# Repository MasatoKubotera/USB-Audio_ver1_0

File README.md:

<html lang="en">
  <head>
    <meta charset="uft-8">
    <meta name="author" content="Masato Kubotera">
  </head>
  <body>
    <h1>USB-Audio Ver. 1.0</h1>
    <h2>About USB-Audio</h2>
    <p>
      USB-Audio is the USB device for audio input/output via a USB interface.
      <br><br>
      <h3>About Ver. 1.0</h3>
      Ver 1.0 has one port for speaker output and two condenser microphones. Since it does not have a speaker, it must be connected via a 2-pin XH connector if necessary. <br>
      The device is used by connecting it to a PC with a USB Mini-B cable.<br>
      The outputs have 0 dB attenuation and the inputs have 3.5 -dB attenuation.
      Each input and output has an "MFB LP filter".
      <br><br>
      <!--
      -->
      <table>
        <tr>
          <td>
            <a href="image/brd_top.png">
              <div align="center">
                
              </div>
            </a>
          </td>
          <td>
            <div align="center">
              
            </div>
          </td>
        </tr>
        <tr>
          <td>
            <div align="center">
              PCB preview image
            </div>
          </td>
          <td>
            <div align="center">
              After component mounting
            </div>
          </td>    
        </tr>
      </table>
    </p>
    <h2>Repository Contents</h2>
    <p>
    <dl>
      <dt>\image</dt>
      <dd>PCB preview images and capture of design screen</dd>
      <dt>\libraries</dt>
      <dd>Libraries used in Autodesk Eagle design</dd>
      <dt>Schematic.pdf</dt>
      <dd>Circuit diagram of this product</dd>
      <dt>BOM.txt</dt>
      <dd>Parts lists output from design data</dd>
      <dt>.brd</dt>
      <dd>Board wiring design file by Autodesk Eagle</dd>
      <dt>.sch</dt>
      <dd>Schematic design file by Autodesk Eagle</dd>
      <dt>Gerber_data.zip</dt>
      <dd>Zip folder of Gerber format files for PCB manufacturing requests.</dd>
      <dt>LICENSE</dt>
      <dd>This is a license to use this product. Please confirm before use.</dd>
      <dt>.gitignore</dt>
      <dd>File to exclude cache files from management.</dd>
    </dl>
    </p>
    <h2>Documentation</h2>
      <p>
        <h3>BOM</h3>
          <table>
            <thead>
              <tr>
                <th> Eagle Design Parts # </th>
                <th> Q'ty </th>
                <th> Mfr. Product # </th>
                <th> Supplier </th>
                <th> Description </th>
              </tr>
            </thead>
              <tr>
                <td>C1, C2, C3, C4, C7, C8, C9, C25</td>
                <td>8</td>
                <td>GRM188R71E105KA12</td>
                <td><a href="https://akizukidenshi.com/catalog/g/gP-14526/">Akizuki</a></td>
                <td>Multilayer Ceramic Capacitors SMD/SMT 1uF 25V 10% 0603</td>
              </tr>
              <tr>
                <td>C10, C13, C15, C16, C21, C22</td>
                <td>6</td>
                <td>UMW1V100MDD</td>
                <td><a href="https://akizukidenshi.com/catalog/g/gP-08377/">Akizuki</a></td>
                <td>Aluminum Electrolytic Capacitors - Radial Leaded 35volts 10uF 85c 5x5 2LS</td>
              </tr>
              <tr>
                <td>C11, C19, C20</td>
                <td>3</td>
                <td>GCD188R71H182KA01J</td>
                <td><a href="https://www.mouser.jp/ProductDetail/81-GCD188R71H182KA1J">Mouser</a></td>
                <td>Multilayer Ceramic Capacitors SMD/SMT 1800pF 50V 10% 0603</td>
              </tr>
              <tr>
                <td>C12, C17, C18</td>
                <td>3</td>
                <td>GRM1882C1H331JA01</td>
                <td><a href="https://akizukidenshi.com/catalog/g/gP-09254/">Akizuki</a></td>
                <td>Multilayer Ceramic Capacitors SMD/SMT 330pF 50V 5% 0603</td>
              </tr>
              <tr>
                <td>C14, C23</td>
                <td>2</td>
                <td>GRM188R6YA106MA73</td>
                <td><a href="https://akizukidenshi.com/catalog/g/gP-13161/">Akizuki</a></td>
                <td>Multilayer Ceramic Capacitors SMD/SMT 10uF 35V 20% 0603</td>
              </tr>
              <tr>
                <td>C24</td>
                <td>1</td>
                <td>GCM188L81H104K57</td>
                <td><a href="https://akizukidenshi.com/catalog/g/gP-16143/">Akizuki</a></td>
                <td>Multilayer Ceramic Capacitors SMD/SMT 0.1uF 50V 10% 0603</td>
              </tr>
              <tr>
                <td>C5, C6</td>
                <td>2</td>
                <td>C1608C0G1H220J080AA</td>
                <td><a href="https://www.mouser.jp/ProductDetail/810-C1608C0G1H220J">Mouser</a></td>
                <td>Multilayer Ceramic Capacitors SMD/SMT 22pF 50V 5% 0603</td>
              </tr>
              <tr>
                <td>CH1</td>
                <td>1</td>
                <td>S2B-XH-A(LF)(SN)</td>
                <td><a href="https://akizukidenshi.com/catalog/g/gC-12262/">Akizuki</a></td>
                <td>Connector Header Through Hole, Side entry 2 position 2.5mm</td>
              </tr>
              <tr>
                <td>CR1</td>
                <td>1</td>
                <td>FA-238V 12.0000MB-K3</td>
                <td><a href="https://akizukidenshi.com/catalog/g/gP-05225/">Akizuki</a></td>
                <td>Crystals 12.0000MHz 50ppm 10pF -40C +85C</td>
              </tr>
              <tr>
                <td>D1, D2</td>
                <td>2</td>
                <td>CG0603MLC-05E</td>
                <td><a href="https://www.mouser.jp/ProductDetail/652-CG0603MLC-05E">Mouser</a></td>
                <td>ESD Protectors 5V 0603</td>
              </tr>
              <tr>
                <td>D3</td>
                <td>1</td>
                <td>RB520SM-30T2R</td>
                <td><a href="https://www.mouser.jp/ProductDetail/755-RB520SM-30T2R">Mouser</a></td>
                <td>Schottky Diodes & Rectifiers Diode Schottky 30V 0.2A</td>
              </tr>
              <tr>
                <td>F1</td>
                <td>1</td>
                <td>MF-MSMF050-2</td>
                <td><a href="https://www.mouser.jp/ProductDetail/652-MF-MSMF050-2">Mouser</a></td>
                <td>PTC Resettable Fuses 15V .5A-HD 100A MAX</td>
              </tr>
              <tr>
                <td>FL1</td>
                <td>1</td>
                <td>BLM18SD220SN1D</td>
                <td><a href="https://www.mouser.jp/ProductDetail/81-BLM18SD220SN1D">Mouser</a></td>
                <td>Ferrite Beads 22 OHM 0603</td>
              </tr>
              <tr>
                <td>IC1</td>
                <td>1</td>
                <td>PCM2904DB</td>
                <td><a href="https://www.mouser.jp/ProductDetail/595-PCM2904DB">Mouser</a></td>
                <td>Interface - CODECs Ster Codec with USB Ifc Sngl-end I/O</td>
              </tr>
              <tr>
                <td>IC2, IC3</td>
                <td>2</td>
                <td>OPA2353UA</td>
                <td><a href="https://www.mouser.jp/ProductDetail/595-OPA2353UA">Mouser</a></td>
                <td>High Speed Operational Amplifiers Hi-Spd Single-Sply Rail-to-Rail</td>
              </tr>
              <tr>
                <td>IC4</td>
                <td>1</td>
                <td>REG103GA-AG4</td>
                <td><a href="https://www.mouser.jp/ProductDetail/595-REG103GA-AG4">Mouser</a></td>
                <td>LDO Voltage Regulators DMOS 500mA LDO Reg</td>
              </tr>
              <tr>
                <td>LED1, LED2</td>
                <td>2</td>
                <td>150060VS86000</td>
                <td><a href="https://www.mouser.jp/ProductDetail/710-150060VS86000">Mouser</a></td>
                <td>Standard LEDs - SMD Green 2V 20mA 573nm 0603</td>
              </tr>
              <tr>
                <td>MIC1, MIC2</td>
                <td>2</td>
                <td>C9767BB422LFP</td>
                <td><a href="https://akizukidenshi.com/catalog/g/gP-01810/">Akizuki</a></td>
                <td>2-wire Electret Condenser Microphone</td>
              </tr>
              <tr>
                <td>R1, R20</td>
                <td>2</td>
                <td>RC0603FR-101KL</td>
                <td><a href="https://www.mouser.jp/ProductDetail/603-RC0603FR-101KL">Mouser</a></td>
                <td>Thick Film Resistors - SMD 1 kOhms 100-200mW 1% 0603</td>
              </tr>
              <tr>
                <td>R11, R12, R13</td>
                <td>3</td>
                <td>RC0603FR-10100RL</td>
                <td><a href="https://www.mouser.jp/ProductDetail/603-RC0603FR-10100RL">Mouser</a></td>
                <td>Thick Film Resistors - SMD 100 Ohms 100-200mW 1% 0603</td>
              </tr>
              <tr>
                <td>R18, R19</td>
                <td>2</td>
                <td>RC0603FR-1018KL</td>
                <td><a href="https://www.mouser.jp/ProductDetail/603-RC0603FR-1018KL">Mouser</a></td>
                <td>Thick Film Resistors - SMD 18 kOhms 100-200mW 1% 0603</td>
              </tr>
              <tr>
                <td>R2, R3</td>
                <td>2</td>
                <td>RC0603FR-1022RL</td>
                <td><a href="https://www.mouser.jp/ProductDetail/603-RC0603FR-1022RL">Mouser</a></td>
                <td>Thick Film Resistors - SMD 22 Ohms 100-200mW 1% 0603</td>
              </tr>
              <tr>
                <td>R4</td>
                <td>1</td>
                <td>RC0603FR-101K5L</td>
                <td><a href="https://www.mouser.jp/ProductDetail/603-RC0603FR-101K5L">Mouser</a></td>
                <td>Thick Film Resistors - SMD 1.5 kOhms 100-200mW 1% 0603</td>
              </tr>
              <tr>
                <td>R5</td>
                <td>1</td>
                <td>RC0603FR-1313KL</td>
                <td><a href="https://www.mouser.jp/ProductDetail/603-RC0603FR-1313KL">Mouser</a></td>
                <td>Thick Film Resistors - SMD 13 kOhms 100-200mW 1% 0603</td>
              </tr>
              <tr>
                <td>R6</td>
                <td>1</td>
                <td>RC0603FR-1027KL</td>
                <td><a href="https://www.mouser.jp/ProductDetail/603-RC0603FR-1027KL">Mouser</a></td>
                <td>Thick Film Resistors - SMD 27 kOhms 100-200mW 1% 0603</td>
              </tr>
              <tr>
                <td>R7</td>
                <td>1</td>
                <td>RC0603FR-101ML</td>
                <td><a href="https://www.mouser.jp/ProductDetail/603-RC0603FR-101ML">Mouser</a></td>
                <td>Thick Film Resistors - SMD 1 MOhms 100-200mW 1% 0603</td>
              </tr>
              <tr>
                <td>R8, R10, R14, R15</td>
                <td>4</td>
                <td>RC0603FR-1312KL</td>
                <td><a href="https://www.mouser.jp/ProductDetail/603-RC0603FR-1312KL">Mouser</a></td>
                <td>Thick Film Resistors - SMD 12 kOhms 100-200mW 1% 0603</td>
              </tr>
              <tr>
                <td>R9, R16, R17</td>
                <td>3</td>
                <td>RC0603FR-103K9L</td>
                <td><a href="https://www.mouser.jp/ProductDetail/603-RC0603FR-103K9L">Mouser</a></td>
                <td>Thick Film Resistors - SMD 3.9 kOhms 100-200mW 1% 0603</td>
              </tr>
              <tr>
                <td>USB1</td>
                <td>1</td>
                <td>MUSB-5B-NE-S175</td>
                <td><a href="https://akizukidenshi.com/catalog/g/gC-05843/">Akizuki</a></td>
                <td>Mini USB Connector  5P B type, Female, SMT type, without standoff</td>
              </tr>
            <tbody>
          </table>          
        <h3>PCB Fabrication</h3>
          PCB(Printed Circuit Board) manufacturing was outsourced to <a href="https://www.elecrow.com/pcb-manufacturing.html">Elecrow</a>.<br>
          The custom specifications are as follows.
          <ul>
            <li>Layer : 2 layers</li>
            <li>Dimensions : 49 x 30</li>
            <li>Different PCB Design : 1eg</li>
            <li>PCB Thickness : 1.6</li>
            <li>PCB Color : Black</li>
            <li>Surface Finish : HASL</li>
            <li>Castellated Hole : No</li>
            <li>Copper Weight : 1oz</li>
            <li>PCB Stencil : Stencil 15cm X 15cm no frame</li>
            <li>Stencil Side : Top</li>
          </ul>
          The data used to order fabrication are as follows.
          <ul>
            <li>Eagle design rule : <a href="https://www.elecrow.com/download/Elecrow_PCB_eagle_rule.zip">Elecrow Eagle Design Rule</a></li>
            <li>Eagle CAM file : <a href="https://www.elecrow.com/download/Elecrow_Gerber_Generater_DrillAlign.zip">Elecrow CAM file</a></li>
            <li>Gerber format data : <a href="/Gerber_data.zip">Gerber_data.zip</a></li>
          </ul>
      </p>
    <h2>Reference</h2>
      <ul>
        <li>Texas Instruments PCM2904DB
          <ul>
            <li><a href="https://www.ti.com/lit/gpn/pcm2904">Stereo Audio CODEC with USB Interface, Single-Ended Analog Input/Output and S/PD datasheet (Rev. C)</a></li>
            <li><a href="https://www.ti.com/lit/pdf/sbfa020">Key Differences Between the PCM290x and PCM290xC</a></li>
        </ul>
        <li><a href="http://sim.okawa-denshi.jp/en/OPtazyuLowkeisan.htm">Multiple Feedback Low-pass Filter Design Tool</a></li>
      </ul>
    <h2>Contact</h2>
    <p>
    If you have any questions, please contact MasatoKubotera, the product's designer, by E-mail.<br>
    E-mail : <a href="mailto:masatokubotera06@yahoo.co.jp">masatokubotera06@yahoo.co.jp</a>
    </p>
    <h2>License Information</h2>
    <p>
      This product is open source.<br>
      Please review the <a href="/LICENSE">LICENSE file</a> for license information.<br>
      <br>
      <strong>USB-Audio Ver. 1.0</strong> by Masato Kubotera is licensed under a <a href="http://creativecommons.org/licenses/by-nc-sa/4.0/">Creative Commons Attribution-NonCommercial-ShareAlike 4.0 International License</a>.
    </p>    
  </body>
</html>

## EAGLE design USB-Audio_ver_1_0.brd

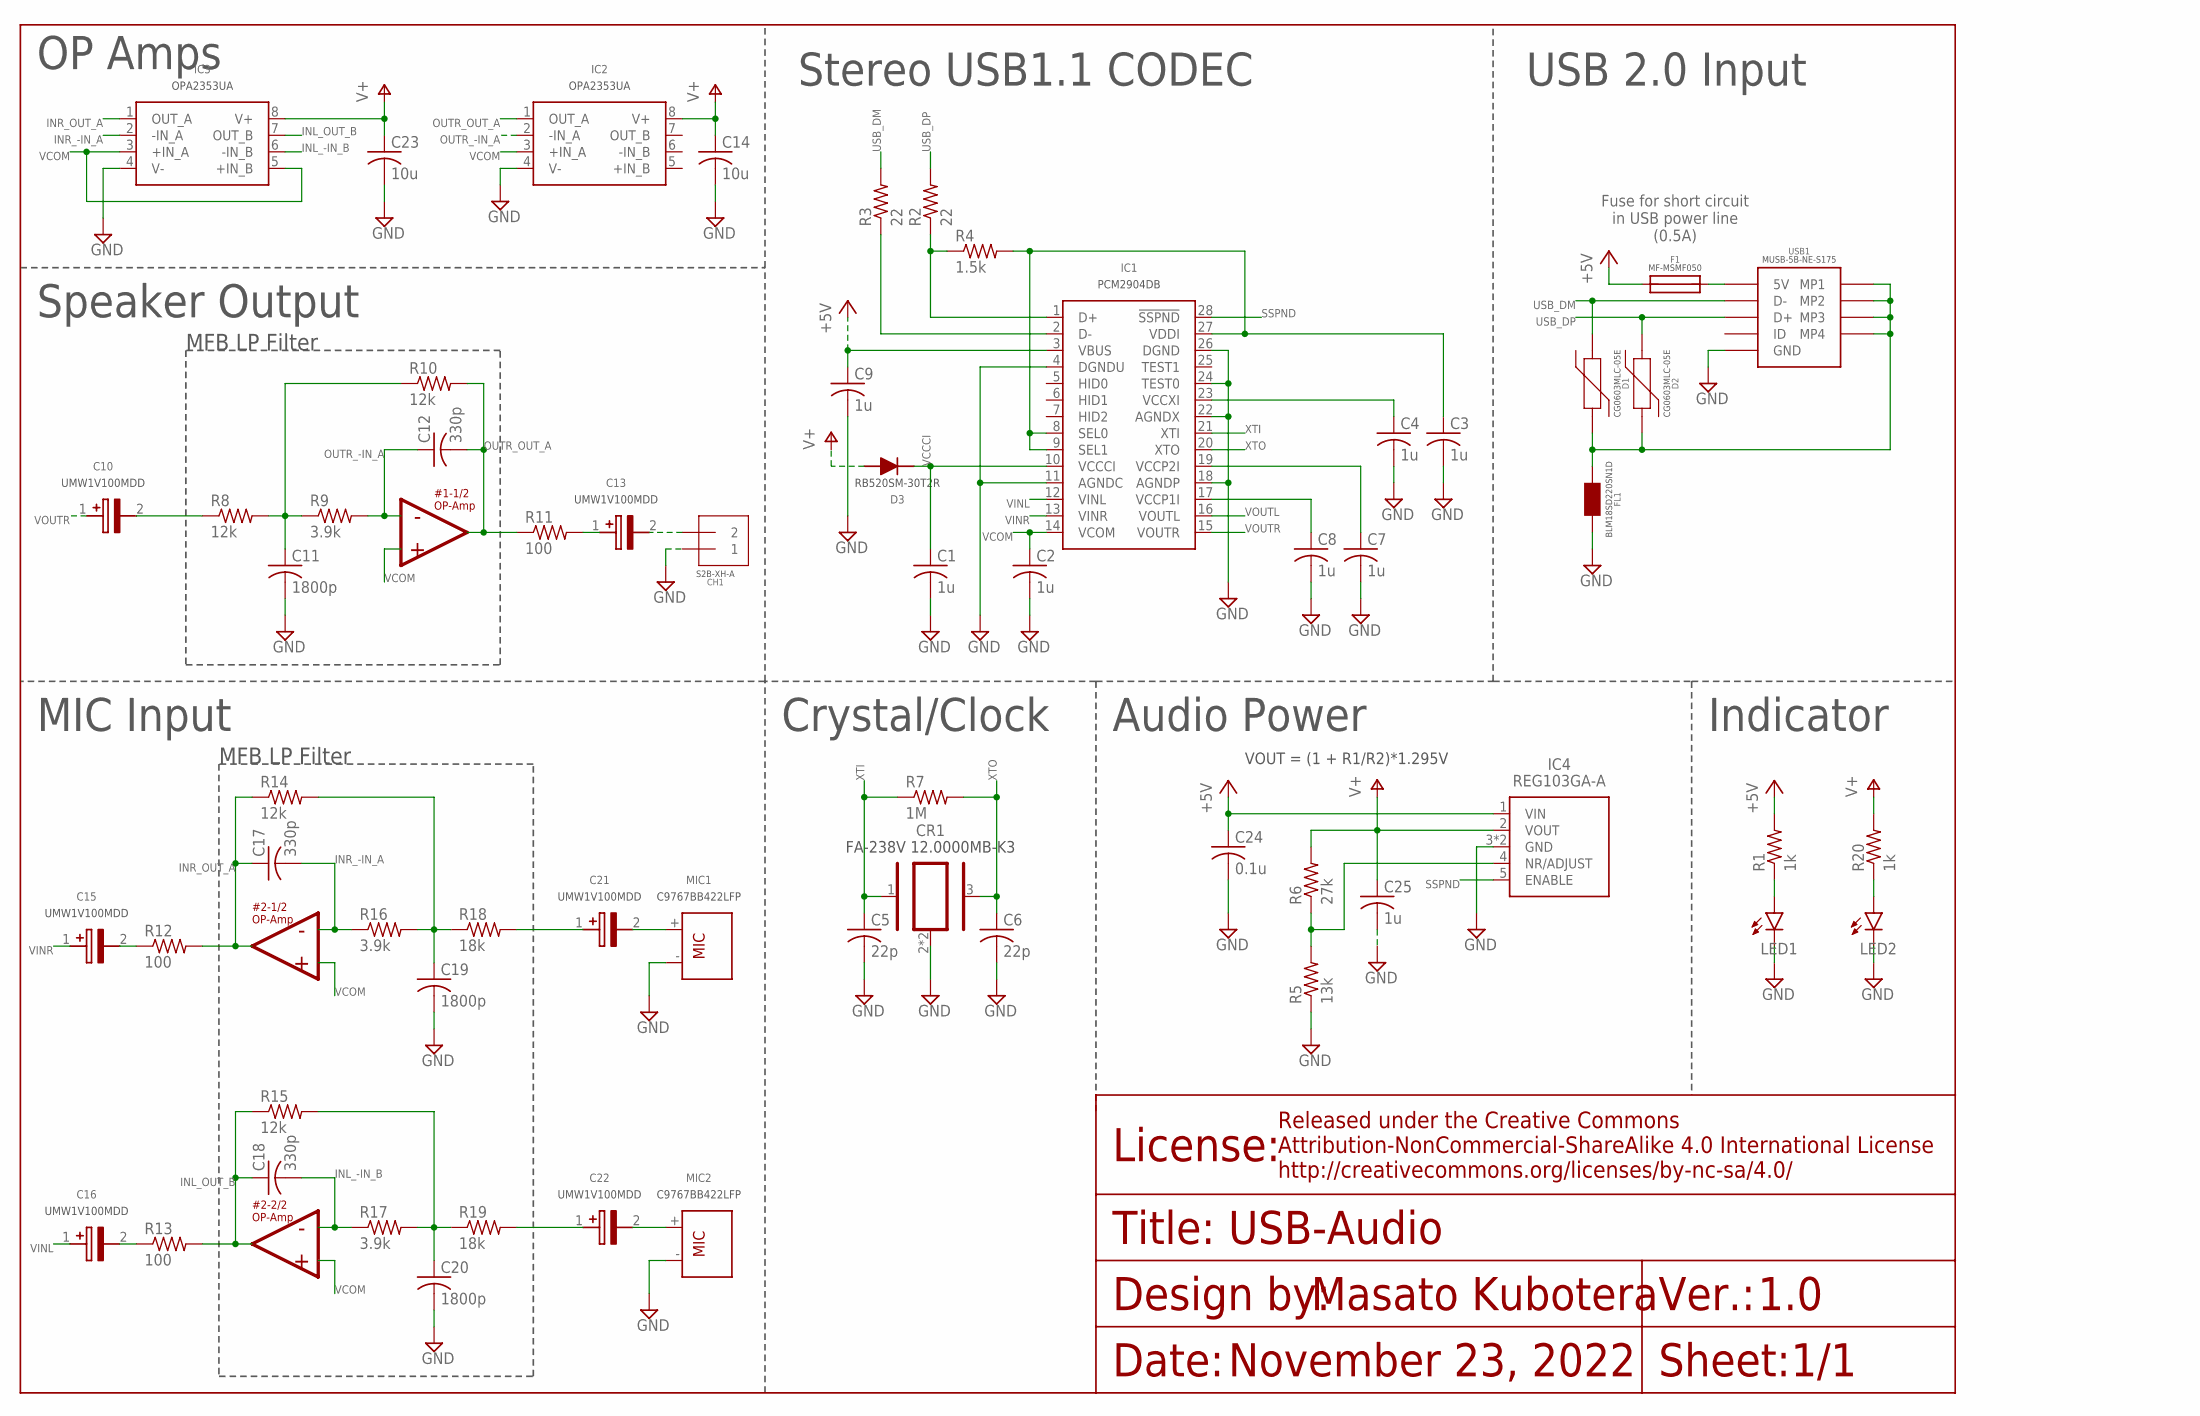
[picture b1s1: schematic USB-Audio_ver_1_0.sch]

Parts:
C1, C2, C3, C4, C7, C8, C9, C25: 1u; C1608
C5, C6: 22p; C1608
C10, C13, C15, C16, C21, C22: UMW1V100MDD
C11, C19, C20: 1800p; C1608
C12, C17, C18: 330p; C1608
C14, C23: 10u; C1608
C24: 0.1u; C1608
CH1: S2B-XH-A
CR1: FA-238V12.0000MB-K3; FA238V
D1, D2: CG0603MLC-05E
D3: RB520SM-30T2R; SOD-523-2
F1: MF-MSMF050
FL1: BLM18SD220SN1D
IC1: PCM2904DB
IC2, IC3: OPA2353UA
IC4: REG103GA-A; SOT223-5
LED1, LED2: LEDSML0603; SML0603
MIC1, MIC2: C9767BB422LFP
R1, R20: 1k; R0603
R2, R3: 22; R0603
R4: 1.5k; R0603
R5: 13k; R0603
R6: 27k; R0603
R7: 1M; R0603
R8, R10, R14, R15: 12k; R0603
R9, R16, R17: 3.9k; R0603
R11, R12, R13: 100; R0603
R18, R19: 18k; R0603
USB1: MINI_USB_B_SMD

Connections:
+5V: C9.1, C24.1, F1.1, IC1.3 (VBUS), IC4.1 (VIN), R1.2
B_FUSE_USB_MINI_B: F1.2, USB1.1 (5V)
DM: IC1.2 (D-), R3.1
DP: IC1.1 (D+), R2.1, R4.1
GND: C1.2, C2.2, C3.2, C4.2, C5.2, C6.2, C7.2, C8.2, C9.2, C11.2, C14.2, C19.2, C20.2, C23.2, C24.2, C25.2, CH1.1, CR1.2, CR1.4, FL1.2, IC1.4 (DGNDU), IC1.11 (AGNDC), IC1.18 (AGNDP), IC1.22 (AGNDX), IC1.24 (TEST0), IC1.26 (DGND), IC2.4 (V-), IC3.4 (V-), IC4.3 (GND), IC4.6 (GND), LED1.C, LED2.C, MIC1.-, MIC2.-, R5.1, USB1.5 (GND)
INL_-IN_B: C18.2, IC3.6 (-IN_B), R17.1
INL_OUT_B: C18.1, IC3.7 (OUT_B), R13.2, R15.1
INR_-IN_A: C17.2, IC3.2 (-IN_A), R16.1
INR_OUT_A: C17.1, IC3.1 (OUT_A), R12.2, R14.1
LED_USBIN: LED1.A, R1.1
LED_USBIN1: LED2.A, R20.1
MIC_INL: C22.2 (-), MIC2.+
MIC_INR: C21.2 (-), MIC1.+
unnamed: C15.2 (-), R12.1
unnamed: C7.1, IC1.19 (VCCP2I)
unnamed: C13.2 (-), CH1.2
unnamed: IC4.4 (NR/ADJUST), R5.2, R6.1
unnamed: C13.1 (+), R11.2
unnamed: C10.2 (-), R8.1
unnamed: C11.1, R8.2, R9.1, R10.1
unnamed: C16.2 (-), R13.1
unnamed: C19.1, R14.2, R16.2, R18.1
unnamed: C21.1 (+), R18.2
unnamed: C22.1 (+), R19.2
unnamed: C20.1, R15.2, R17.2, R19.1
OUTR_-IN_A: C12.1, IC2.2 (-IN_A), R9.2
OUTR_OUT_A: C12.2, IC2.1 (OUT_A), R10.2, R11.1
SSPND: C8.1, IC1.17 (VCCP1I), IC1.28 (!SSPND), IC4.5 (ENABLE)
USB_DM: D1.1, R3.2, USB1.2 (D-)
USB_DP: D2.1, R2.2, USB1.3 (D+)
USB_MINI_B_SHIELD: D1.2, D2.2, FL1.1, USB1.MP1, USB1.MP2, USB1.MP3, USB1.MP4
V+: C14.1, C23.1, C25.1, D3.2 (A), IC2.8 (V+), IC3.8 (V+), IC4.2 (VOUT), R6.2, R20.2
VCCCI: C1.1, D3.1 (K), IC1.10 (VCCCI)
VCCXI: C4.1, IC1.23 (VCCXI)
VCOM: C2.1, IC1.14 (VCOM), IC2.3 (+IN_A), IC3.3 (+IN_A), IC3.5 (+IN_B)
VDDI: C3.1, IC1.8 (SEL0), IC1.9 (SEL1), IC1.27 (VDDI), R4.2
VINL: C16.1 (+), IC1.12 (VINL)
VINR: C15.1 (+), IC1.13 (VINR)
VOUTL: IC1.16 (VOUTL)
VOUTR: C10.1 (+), IC1.15 (VOUTR)
XTI: C5.1, CR1.1, IC1.21 (XTI), R7.1
XTO: C6.1, CR1.3, IC1.20 (XTO), R7.2

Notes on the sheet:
1.0
1/1
November 23, 2022
USB-Audio
USB 2.0 Input
Fuse for short circuit in USB power line (0.5A)
VOUT = (1 + R1/R2)*1.295V
Audio Power
Stereo USB1.1 CODEC
MIC Input
Crystal/Clock
Speaker Output
#2-1/2 OP-Amp
#2-2/2 OP-Amp
MFB LP Filter
#1-1/2 OP-Amp
Indicator
OP Amps

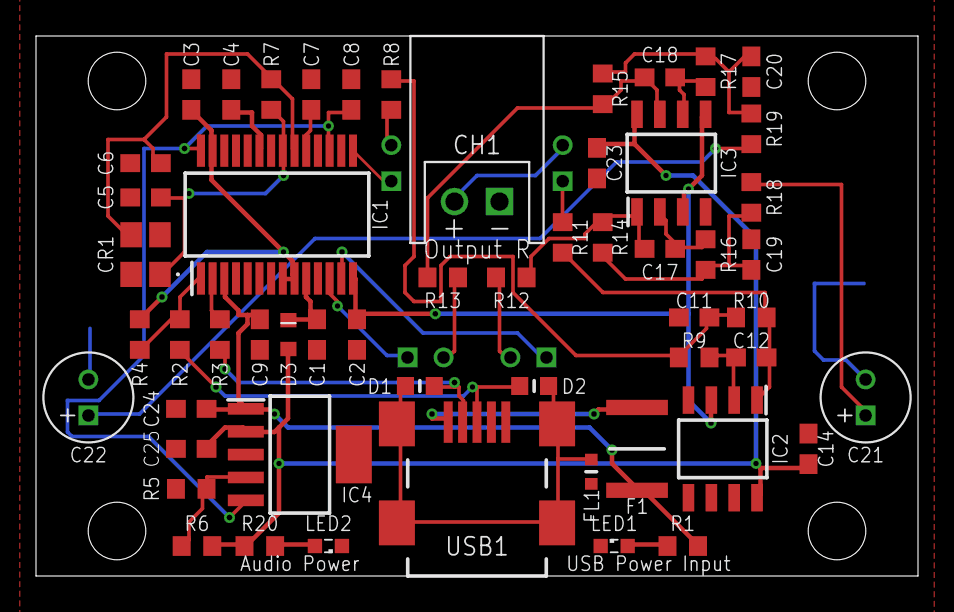
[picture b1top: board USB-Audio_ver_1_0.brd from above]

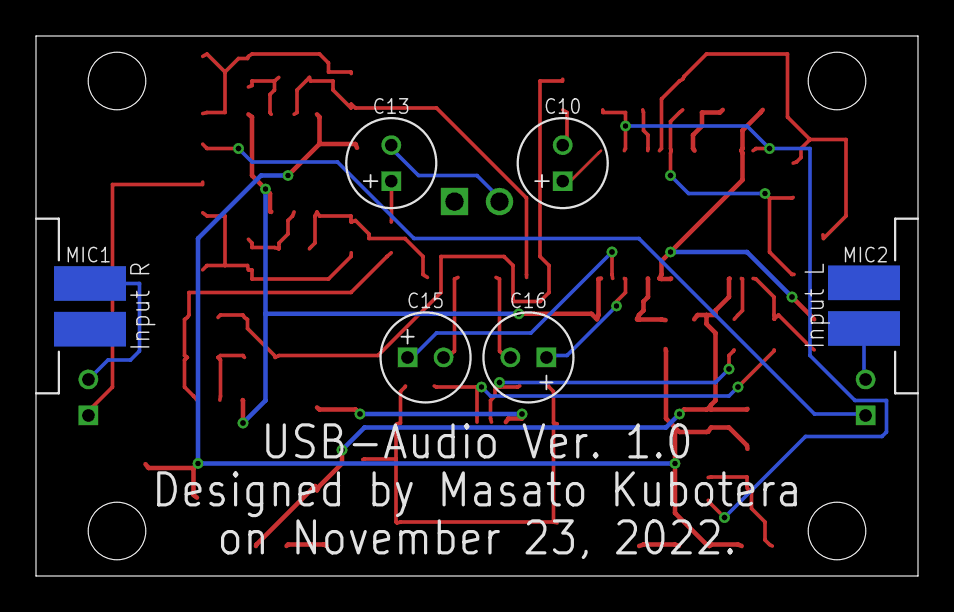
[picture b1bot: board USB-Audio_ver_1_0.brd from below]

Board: 2 copper layers, 49.0 x 30.0 mm, 61 parts (6 on the bottom side), 41 nets.

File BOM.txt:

Partlist exported from C:/Users/Masato/Documents/EAGLE/projects/USB-Audio_ver1_0/USB-Audio_ver_1_0.sch at 2022/11/11 22:42

Qty Value               Device              Package        Parts                           Description                
2                       LEDSML0603          SML0603        LED1, LED2                      LED                        
1   0.1u                C-USC1608           C1608          C24                             CAPACITOR, American symbol 
1   1.5k                R-US_R0603          R0603          R4                              RESISTOR, American symbol  
3   100                 R-US_R0603          R0603          R11, R12, R13                   RESISTOR, American symbol  
2   10u                 C-USC1608           C1608          C14, C23                        CAPACITOR, American symbol 
4   12k                 R-US_R0603          R0603          R8, R10, R14, R15               RESISTOR, American symbol  
1   13k                 R-US_R0603          R0603          R5                              RESISTOR, American symbol  
3   1800p               C-USC1608           C1608          C11, C19, C20                   CAPACITOR, American symbol 
2   18k                 R-US_R0603          R0603          R18, R19                        RESISTOR, American symbol  
1   1M                  R-US_R0603          R0603          R7                              RESISTOR, American symbol  
2   1k                  R-US_R0603          R0603          R1, R20                         RESISTOR, American symbol  
8   1u                  C-USC1608           C1608          C1, C2, C3, C4, C7, C8, C9, C25 CAPACITOR, American symbol 
2   22                  R-US_R0603          R0603          R2, R3                          RESISTOR, American symbol  
2   22p                 C-USC1608           C1608          C5, C6                          CAPACITOR, American symbol 
1   27k                 R-US_R0603          R0603          R6                              RESISTOR, American symbol  
3   3.9k                R-US_R0603          R0603          R9, R16, R17                    RESISTOR, American symbol  
3   330p                C-USC1608           C1608          C12, C17, C18                   CAPACITOR, American symbol 
1   BLM18SD220SN1D      BLM18SD220SN1D      BLM18SD220SN1D FL1                                                        
2   C9767BB422LFP       C9767BB422LFP       C9767BB422LFP  MIC1, MIC2                                                 
2   CG0603MLC-05E       CG0603MLC-05E       CG0603MLC-05E  D1, D2                                                     
1   FA-238V12.0000MB-K3 FA-238V12.0000MB-K3 FA238V         CR1                                                        
1   MF-MSMF050          MF-MSMF050          MF-MSMF050     F1                                                         
1   MINI_USB_B_SMD      MINI_USB_B_SMD      MINI_USB_B_SMD USB1                                                       
2   OPA2353UA           OPA2353UA           OPA2353UA      IC2, IC3                                                   
1   PCM2904DB           PCM2904DB           PCM2904DB      IC1                                                        
1   RB520SM-30T2R       RB520SM-30T2R       SOD-523-2      D3                                                         
1   REG103GA-A          REG103GA-A          SOT223-5       IC4                                                        
1   S2B-XH-A            S2B-XH-A            S2B-XH-A       CH1                                                        
6   UMW1V100MDD         UMW1V100MDD         UMW1V100MDD    C10, C13, C15, C16, C21, C22

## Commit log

2022-11-21 Initial upload of data
2022-11-23 Modified power supply and silk printing
2022-12-29 update images

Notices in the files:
parts and their libraries:
Frame: Released under the Creative Commons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
